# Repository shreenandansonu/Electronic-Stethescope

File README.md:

# **EKOBIT** | Electronics Stethoscope

This project aims at making an affordable yet powerful **electronics stethoscope** to **record and listen** to the Heart and Lungs Sound. The stethoscope would be primarily used for teaching purposes for medical students at CMC Vellore, Bagayam Campus, Vellore, Tamil Nadu India. Below mentioned are the objective.

---

### **OBJECTIVE**
---
| Objectives | Status |
| :-------------------------------------------: | :-------------------------: |
| Connect stethoscope to a microphone to capture sounds. |  |
| Amplify heart and lung sounds using custom circuits. |   |
| Filter captured sounds using built electronic circuits. |   |
| Transfer audio to PC/mobile via 3.5 mm jack. |   |
| Record and save audio using open-source/custom software. |   |

```
Digitial Version of this device is in progress........
```

## **DEMO**
[EKOBIT DEMO VIDEO](https://youtu.be/8x4jnvdGgfg?si=aJdlGi542GCe0jYr)
---

## **SOFTWARE**
[SOFTWARE DOWNLOAD](https://cmcekobit.netlify.app/)
---

## **DOCUMENTATION**
[DOCUMENTATION DOWNLOAD](https://cmcekobit.netlify.app/EKOBIT.pdf)
---

| Top View | Bottom View |
| :-------------------------------------------: | :-------------------------: |
|   |   |

---
| PCB Layout | Schematics |
| :-------------------------------------------: | :-------------------------------------------: |
|   |  |

---
| Stethoscope Connector | Stethoscope Enclouser |
| :-------------------------------------------: | :-------------------------------------------: |
|   |  |

### **RAW VS PROCESSED** signal DSO

### **RECORDING SOFTWARE**

### **SPECTOGRAM OF RECORDED SOUND**

---
### **FINAL DEVICE DEVELOPED**
| **FINAL PRODUCT** | **HARDWARE** |
| :-------------------------------------------: | :-------------------------: |
| |  |
| |  |
| |  |
| |  |

---
### **BEHIND THE DEVELOPMENT**
| **PRODUCT DEVELOPMENT** | **PROTOTYPING** |
| :-------------------------------------------: | :-------------------------: |
| |  |
| |  |
| |  |
| |  |

## **SECOND VERSION IN PROGRESS**
|SMD VERSION|
|----|
||

## License

- Software is licensed under the [MIT License](LICENSE).
- Hardware is licensed under the [CERN-OHL-S v2 License](LICENSE-CERN-OHL-S).

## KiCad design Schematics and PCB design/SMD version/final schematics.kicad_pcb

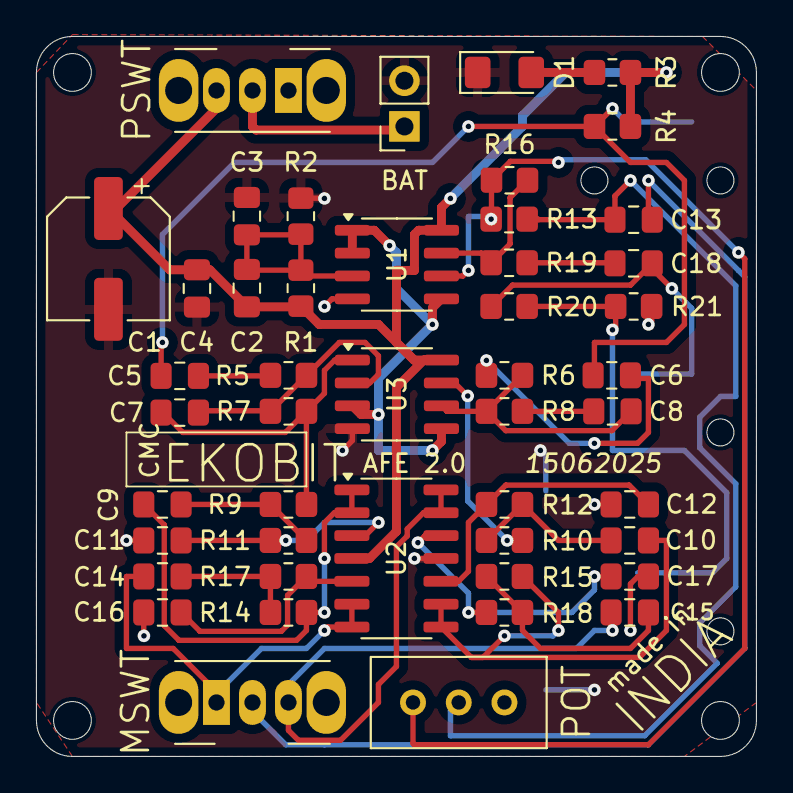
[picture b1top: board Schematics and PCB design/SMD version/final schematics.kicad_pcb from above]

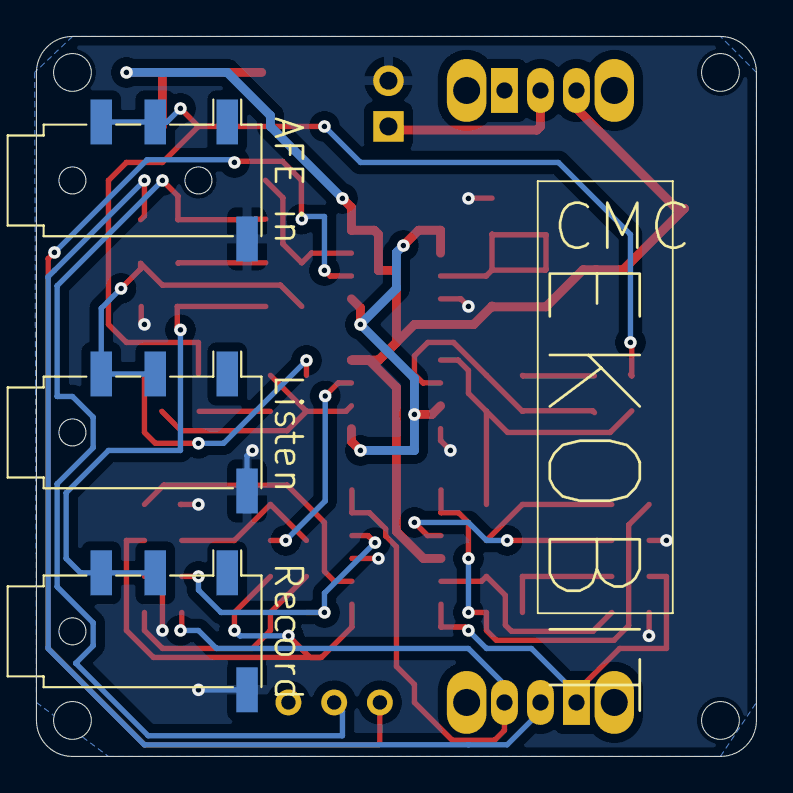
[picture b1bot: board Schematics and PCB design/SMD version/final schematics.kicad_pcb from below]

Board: 2 copper layers, 40.0 x 40.0 mm, 54 parts (3 on the bottom side), 33 nets.

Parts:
AFE in: AFE In; Jack_3.5mm_PJ320D_Horizontal
BAT: PWR; PinSocket_1x02_P2.54mm_Vertical
C1: 47uF; CP_Elec_6.3x5.4
C2, C3, C4, C5: 100nF; C_0805_2012Metric_Pad1.18x1.45mm_HandSolder
C6: 47nF; C_0805_2012Metric_Pad1.18x1.45mm_HandSolder
C7, C9, C11, C14, C16: 220pF; C_0805_2012Metric_Pad1.18x1.45mm_HandSolder
C8, C10, C12, C15, C17: 82pF; C_0805_2012Metric_Pad1.18x1.45mm_HandSolder
C13, C18: 10uF; C_0805_2012Metric_Pad1.18x1.45mm_HandSolder
D1: LED; LED_1206_3216Metric_Pad1.42x1.75mm_HandSolder
H1, H2, H3, H4: MountingHole; MountingHole_2.1mm
Listen: HeadPhone; Jack_3.5mm_PJ320D_Horizontal
MSWT: Op Mode; SW_Slide_SPDT_Angled_CK_OS102011MA1Q
POT: 10K pot; Potentiometer_Bourns_3296W_Vertical
PSWT: PSWT; SW_Slide_SPDT_Angled_CK_OS102011MA1Q
R1, R2: 100K; R_0805_2012Metric_Pad1.20x1.40mm_HandSolder
R3, R4: 1K; R_0805_2012Metric_Pad1.20x1.40mm_HandSolder
R5, R6: 47K; R_0805_2012Metric_Pad1.20x1.40mm_HandSolder
R7, R8, R9, R10, R11, R12, R14, R15, R17, R18: 1M; R_0805_2012Metric_Pad1.20x1.40mm_HandSolder
R13, R16: 20K; R_0805_2012Metric_Pad1.20x1.40mm_HandSolder
R19: 100; R_0805_2012Metric_Pad1.20x1.40mm_HandSolder
R20, R21: 10K; R_0805_2012Metric_Pad1.20x1.40mm_HandSolder
Record: Record; Jack_3.5mm_PJ320D_Horizontal
U1, U3: NE5532; SOIC-8_3.9x4.9mm_P1.27mm
U2: TL074; SOIC-14_3.9x8.7mm_P1.27mm

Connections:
2.5V: U1.1, U1.2 (-), U1.5 (+), U3.3 (+), U3.5 (+)
+5V: C1.1, C2.1, C4.1, PSWT.3 (A), R1.1, R3.1, R4.2, U1.8 (V+), U2.4 (V+), U3.8 (V+)
FSignal: C18.2, Listen.R1, Listen.R2, R20.1
GND: AFE in.S, BAT.2, C1.2, C3.2, C4.2, C11.2, C12.2, C16.2, C17.2, D1.1 (K), Listen.S, R2.2, R21.2, Record.S, U1.4 (V-), U2.11 (V-), U3.4 (V-)
Heart: C14.1, MSWT.1 (C), U2.6 (-), U2.7
Lungs: C15.1, MSWT.3 (A), U2.13 (-), U2.14
unnamed: C5.2, R5.1
unnamed: C6.2, R6.1
unnamed: C7.2, R7.2, R9.1, U3.1
unnamed: C8.2, R8.2
unnamed: C9.2, R9.2, R11.1
unnamed: C10.2, R10.2, R12.1
unnamed: C13.2, POT.2, R13.1
unnamed: C14.2, R14.1, R17.1
unnamed: C15.2, R15.2, R18.1
unnamed: C18.1, R19.2
unnamed: D1.2 (A), R3.2
unnamed: R20.2, R21.1, Record.R1, Record.R2
unnamed: R10.1, U3.7
unnamed: R16.2, R19.1, U1.7
unnamed: C13.1, MSWT.2 (B)
unnamed: C2.2, C3.1, R1.2, R2.1, U1.3 (+)
unnamed: POT.3, R13.2, R16.1, U1.6 (-)
unnamed: C11.1, R11.2, U2.3 (+)
unnamed: C9.1, R14.2, U2.1, U2.2 (-)
unnamed: C16.1, R17.2, U2.5 (+)
unnamed: C12.1, R12.2, U2.10 (+)
unnamed: C10.1, R15.1, U2.8, U2.9 (-)
unnamed: C17.1, R18.2, U2.12 (+)
unnamed: C7.1, R5.2, R7.1, U3.2 (-)
unnamed: C8.1, R6.2, R8.1, U3.6 (-)
Signal: AFE in.R1, AFE in.R2, C5.1, C6.1, R4.1
switch: BAT.1, PSWT.2 (B)

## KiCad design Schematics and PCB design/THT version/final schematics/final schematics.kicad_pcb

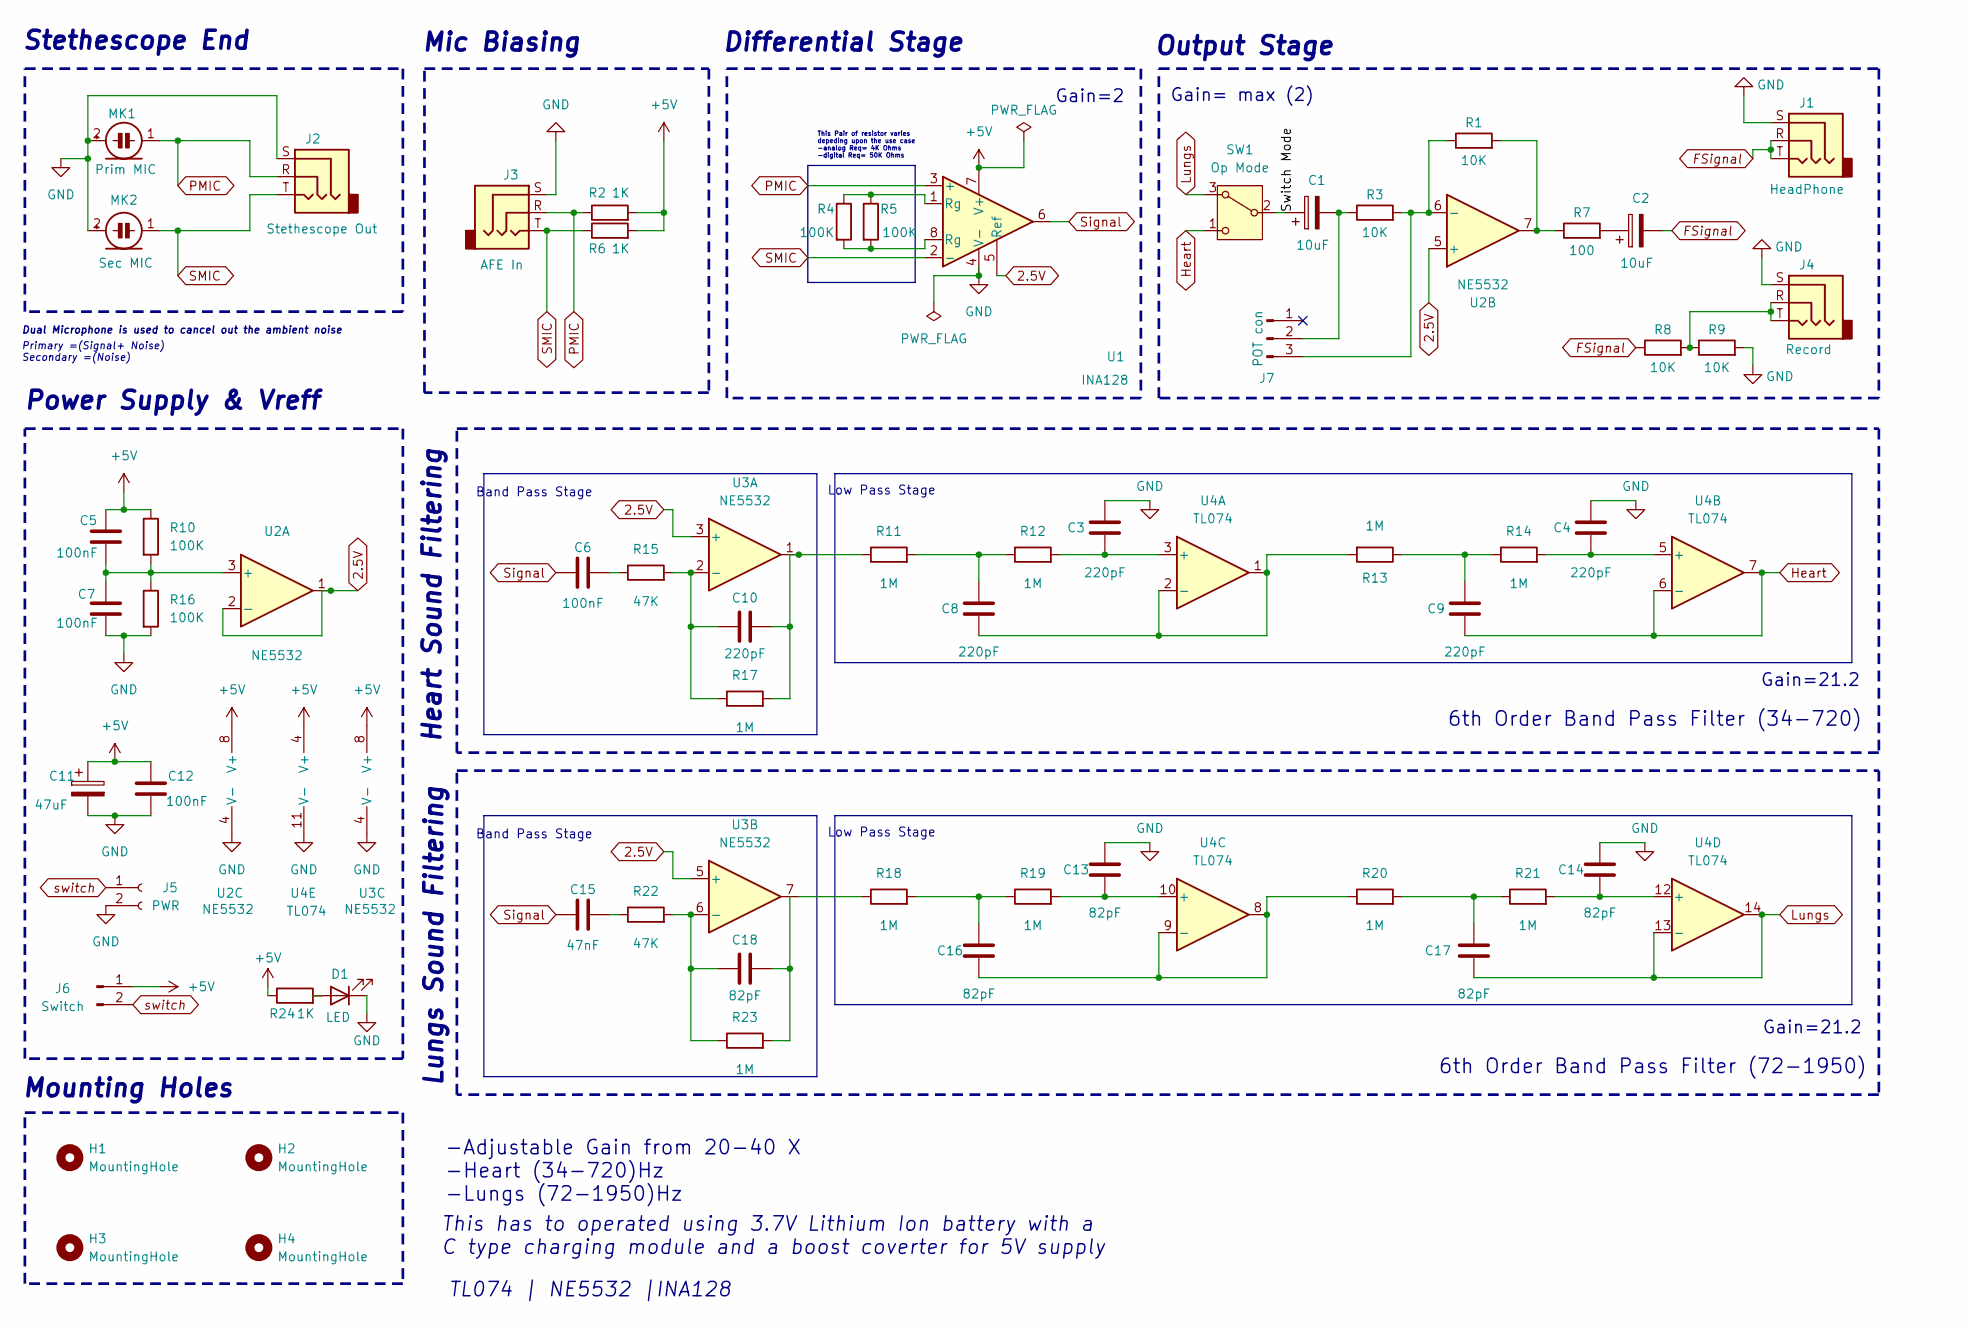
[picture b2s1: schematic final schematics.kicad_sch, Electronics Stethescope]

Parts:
C1, C2: 10uF; CP_Radial_D5.0mm_P2.50mm
C3, C4, C8, C9, C10: 220pF; C_Disc_D3.0mm_W2.0mm_P2.50mm
C5, C6, C7, C12: 100nF; C_Disc_D3.0mm_W2.0mm_P2.50mm
C11: 47uF; CP_Radial_D5.0mm_P2.50mm
C13, C14, C16, C17, C18: 82pF; C_Disc_D3.0mm_W2.0mm_P2.50mm
C15: 47nF; C_Disc_D3.0mm_W2.0mm_P2.50mm
D1: LED; LED_D3.0mm_Clear
H1, H2, H3, H4: MountingHole; MountingHole_2.1mm
J1: HeadPhone; Jack_3.5mm_Ledino_KB3SPRS_Horizontal
J2: Stethescope Out
J3: AFE In; Jack_3.5mm_Ledino_KB3SPRS_Horizontal
J4: Record; Jack_3.5mm_Ledino_KB3SPRS_Horizontal
J5: PWR; JST_EH_B2B-EH-A_1x02_P2.50mm_Vertical
J6: Switch; JST_EH_B2B-EH-A_1x02_P2.50mm_Vertical
J7: POT con; PinHeader_1x03_P2.54mm_Vertical
MK1: Prim MIC
MK2: Sec MIC
R1, R3, R8, R9: 10K; R_Axial_DIN0207_L6.3mm_D2.5mm_P7.62mm_Horizontal
R2, R6, R24: 1K; R_Axial_DIN0207_L6.3mm_D2.5mm_P7.62mm_Horizontal
R4, R5, R10, R16: 100K; R_Axial_DIN0207_L6.3mm_D2.5mm_P7.62mm_Horizontal
R7: 100; R_Axial_DIN0207_L6.3mm_D2.5mm_P7.62mm_Horizontal
R11, R12, R13, R14, R17, R18, R19, R20, R21, R23: 1M; R_Axial_DIN0207_L6.3mm_D2.5mm_P7.62mm_Horizontal
R15, R22: 47K; R_Axial_DIN0207_L6.3mm_D2.5mm_P7.62mm_Horizontal
SW1: Op Mode; SW_Slide_SPDT_Angled_CK_OS102011MA1Q
U1: INA128; DIP-8_W7.62mm
U2, U3: NE5532; DIP-8_W7.62mm
U4: TL074; DIP-14_W7.62mm

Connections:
2.5V: U1.5 (Ref), U2.1, U2.2 (-), U2.5 (+), U3.3 (+), U3.5 (+)
+5V: C5.1, C11.1, C12.1, J6.1, R2.2, R6.2, R10.1, R24.1, U1.7 (V+), U2.8 (V+), U3.8 (V+), U4.4 (V+)
FSignal: C2.2, J1.R, J1.T, R8.1
GND: C3.2, C4.2, C7.2, C11.2, C12.2, C13.2, C14.2, D1.1 (K), J1.S, J2.S, J3.S, J4.S, J5.2, MK1.2 (+), MK2.2 (+), R9.2, R16.2, U1.4 (V-), U2.4 (V-), U3.4 (V-), U4.11 (V-)
Heart: C9.1, SW1.1 (C), U4.6 (-), U4.7
Lungs: C17.1, SW1.3 (A), U4.13 (-), U4.14
unnamed: C2.1, R7.2
unnamed: C6.2, R15.1
unnamed: C8.2, R11.2, R12.1
unnamed: C9.2, R13.1, R14.1
unnamed: C10.2, R11.1, R17.2, U3.1
unnamed: C15.2, R22.1
unnamed: C16.2, R18.2, R19.1
unnamed: C17.2, R20.2, R21.1
unnamed: C18.2, R23.2
unnamed: D1.2 (A), R24.2
unnamed: J4.R, J4.T, R8.2, R9.1
unnamed: C1.2, J7.2, R3.1
unnamed: J7.3, R1.1, R3.2, U2.6 (-)
unnamed: R1.2, R7.1, U2.7
unnamed: R4.1, R5.1, U1.1 (Rg)
unnamed: R4.2, R5.2, U1.8 (Rg)
unnamed: R18.1, U3.7
unnamed: C1.1, SW1.2 (B)
unnamed: C5.2, C7.1, R10.2, R16.1, U2.3 (+)
unnamed: C10.1, R15.2, R17.1, U3.2 (-)
unnamed: C18.1, R22.2, R23.1, U3.6 (-)
unnamed: C3.1, R12.2, U4.3 (+)
unnamed: C8.1, R13.2, U4.1, U4.2 (-)
unnamed: C4.1, R14.2, U4.5 (+)
unnamed: C13.1, R19.2, U4.10 (+)
unnamed: C16.1, R20.1, U4.8, U4.9 (-)
unnamed: C14.1, R21.2, U4.12 (+)
PMIC: J2.R, J3.R, MK1.1 (-), R2.1, U1.3 (+)
SMIC: J2.T, J3.T, MK2.1 (-), R6.1, U1.2 (-)
Signal: C6.1, C15.1, U1.6
switch: J5.1, J6.2

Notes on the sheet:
Heart Sound Filtering
Gain=2
Low Pass Stage
This has to operated using 3.7V Lithium Ion battery with a C type charging module and a boost coverter for 5V supply
Gain= max (2)
Mounting Holes
Differential Stage
Gain=21.2
6th Order Band Pass Filter (72-1950)
Primary =(Signal+ Noise) Secondary =(Noise)
This Pair of resistor varies depeding upon the use case -analog Req= 4K Ohms -digital Req= 50K Ohms
6th Order Band Pass Filter (34-720)
Output Stage
Lungs Sound Filtering
Stethescope End
Band Pass Stage
Power Supply & Vreff
-Adjustable Gain from 20-40 X -Heart (34-720)Hz -Lungs (72-1950)Hz
TL074 | NE5532 |INA128
Dual Microphone is used to cancel out the ambient noise
Mic Biasing

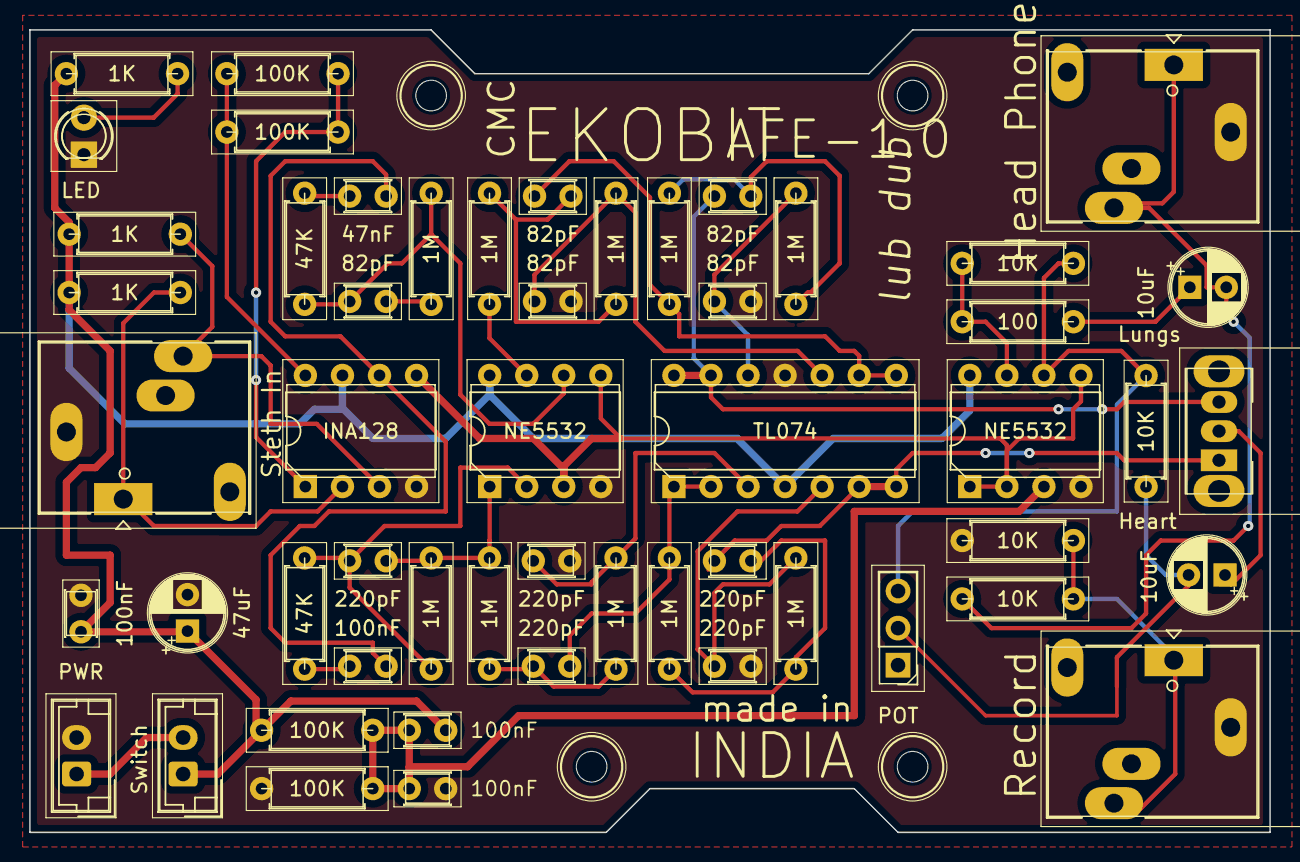
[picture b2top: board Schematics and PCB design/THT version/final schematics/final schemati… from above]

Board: 2 copper layers, 85.0 x 55.0 mm, 58 parts (0 on the bottom side), 37 nets.

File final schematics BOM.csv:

"Reference","Value","Datasheet","Footprint","Qty","DNP"
"C1,C2","10uF","~","Capacitor_THT:CP_Radial_D5.0mm_P2.50mm","2",""
"C3,C4,C8,C9,C10","220pF","~","Capacitor_THT:C_Disc_D3.0mm_W2.0mm_P2.50mm","5",""
"C5,C6,C7,C12","100nF","~","Capacitor_THT:C_Disc_D3.0mm_W2.0mm_P2.50mm","4",""
"C11","47uF","~","Capacitor_THT:CP_Radial_D5.0mm_P2.50mm","1",""
"C13,C14,C16,C17,C18","82pF","~","Capacitor_THT:C_Disc_D3.0mm_W2.0mm_P2.50mm","5",""
"C15","47nF","~","Capacitor_THT:C_Disc_D3.0mm_W2.0mm_P2.50mm","1",""
"D1","LED","~","LED_THT:LED_D3.0mm_Clear","1",""
"J1","HeadPhone","~","Connector_Audio:Jack_3.5mm_Ledino_KB3SPRS_Horizontal","1",""
"J2","Stethescope Out","~","","1",""
"J3","AFE In","~","Connector_Audio:Jack_3.5mm_Ledino_KB3SPRS_Horizontal","1",""
"J4","Record","~","Connector_Audio:Jack_3.5mm_Ledino_KB3SPRS_Horizontal","1",""
"J5","PWR","~","Connector_JST:JST_EH_B2B-EH-A_1x02_P2.50mm_Vertical","1",""
"J6","Switch","~","Connector_JST:JST_EH_B2B-EH-A_1x02_P2.50mm_Vertical","1",""
"J7","POT con","~","Connector_PinHeader_2.54mm:PinHeader_1x03_P2.54mm_Vertical","1",""
"MK1","Prim MIC","~","","1",""
"MK2","Sec MIC","~","","1",""
"R1,R3,R8,R9","10K","~","Resistor_THT:R_Axial_DIN0207_L6.3mm_D2.5mm_P7.62mm_Horizontal","4",""
"R2,R6,R24","1K","~","Resistor_THT:R_Axial_DIN0207_L6.3mm_D2.5mm_P7.62mm_Horizontal","3",""
"R4,R5,R10,R16","100K","~","Resistor_THT:R_Axial_DIN0207_L6.3mm_D2.5mm_P7.62mm_Horizontal","4",""
"R7","100","~","Resistor_THT:R_Axial_DIN0207_L6.3mm_D2.5mm_P7.62mm_Horizontal","1",""
"R11,R12,R13,R14,R17,R18,R19,R20,R21,R23","1M","~","Resistor_THT:R_Axial_DIN0207_L6.3mm_D2.5mm_P7.62mm_Horizontal","10",""
"R15,R22","47K","~","Resistor_THT:R_Axial_DIN0207_L6.3mm_D2.5mm_P7.62mm_Horizontal","2",""
"SW1","Op Mode","~","Button_Switch_THT:SW_Slide_SPDT_Angled_CK_OS102011MA1Q","1",""
"U1","INA128","http://www.ti.com/lit/ds/symlink/ina128.pdf","Package_DIP:DIP-8_W7.62mm","1",""
"U2,U3","NE5532","http://www.ti.com/lit/ds/symlink/ne5532.pdf","Package_DIP:DIP-8_W7.62mm","2",""
"U4","TL074","http://www.ti.com/lit/ds/symlink/tl071.pdf","Package_DIP:DIP-14_W7.62mm","1",""

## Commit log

2025-07-05 first
2025-07-05 Second
2025-07-05 change
2025-07-05 tutorial
2025-07-05 demo
2025-07-05 spectro
2025-07-05 sepcto
2025-07-05 check
2025-07-05 pics done
2025-07-05 done almost
2025-07-05 final done
2025-07-05 new images
2025-07-05 website
2025-07-05 done
2025-07-05 changed
2025-07-05 good done
2025-07-05 squared
2025-07-05 done all
2025-07-05 don done done
2025-07-05 madeinindia
2025-07-07 color updates
2025-07-13 licence
2025-07-13 Create LICENSE
2025-07-13 license
2025-07-13 Create LICENSE-SOFTWARE
2025-07-13 Create LICENSE-HARDWARE
2025-07-13 Update LICENSE-HARDWARE
2025-07-13 all done
2025-07-13 Update LICENSE-CERN-OHL-S
2025-07-16 documentation complete
2025-07-16 done doc
2025-08-09 relative path
2025-10-23 demo sound added
2025-10-23 demo removed
2026-03-13 gif added
2026-03-13 image added
2026-03-13 second version added
2026-03-14 Change Pics

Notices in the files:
README.md:
License: MIT
License: CERN-OHL-S v2
